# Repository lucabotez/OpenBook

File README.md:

Botez Luca, 334CA

# OpenBook

## About
This project is a minimalist eBook Reader called OpenBook, built on the ESP32-C6 platform and equipped with a 7.5-inch e-paper display, a Li-Po battery, USB-C charging, and physical control buttons.

The device is designed to be energy-efficient and easy to use, featuring a simple interface controlled via GPIOs, with text display functions aimed at providing an optimal e-reading experience.

## Block Diagram

## BOM (Bill of Materials)

| Component | Purchase Link | Datasheet |
|-----------|---------------|-----------|
| BOOT_BUTTON | [https://ro.mouser.com/ProductDetail/Panasonic/EVQ-P7L01P](https://ro.mouser.com/ProductDetail/Panasonic/EVQ-P7L01P?qs=rJ%252BziJWpyszWhhNszc02jQ%3D%3D&_gl=1*xzqk3l*_ga*dW5kZWZpbmVk*_ga_15W4STQT4T*dW5kZWZpbmVk*_ga_1KQLCYKRX3*dW5kZWZpbmVk) | https://componentsearchengine.com/Datasheets/2/EVQP7L01P.pdf |
| C1 | [https://ro.mouser.com/ProductDetail/YAGEO/CC0402MRX5R5BB106](https://ro.mouser.com/ProductDetail/YAGEO/CC0402MRX5R5BB106?qs=zEY9bCHj09eCmUJdZuS5Lg%3D%3D) | https://componentsearchengine.com/Datasheets/2/CC0402MRX5R5BB106.pdf |
| C1_BAT | [https://ro.mouser.com/ProductDetail/YAGEO/CC0402MRX5R5BB106](https://ro.mouser.com/ProductDetail/YAGEO/CC0402MRX5R5BB106?qs=zEY9bCHj09eCmUJdZuS5Lg%3D%3D) | https://componentsearchengine.com/Datasheets/2/CC0402MRX5R5BB106.pdf |
| C1_BAT2 | [https://ro.mouser.com/ProductDetail/YAGEO/CC0402MRX5R5BB106](https://ro.mouser.com/ProductDetail/YAGEO/CC0402MRX5R5BB106?qs=zEY9bCHj09eCmUJdZuS5Lg%3D%3D) | https://componentsearchengine.com/Datasheets/2/CC0402MRX5R5BB106.pdf |
| C2 | [https://ro.mouser.com/ProductDetail/YAGEO/CC0402MRX5R5BB106](https://ro.mouser.com/ProductDetail/YAGEO/CC0402MRX5R5BB106?qs=zEY9bCHj09eCmUJdZuS5Lg%3D%3D) | https://componentsearchengine.com/Datasheets/2/CC0402MRX5R5BB106.pdf |
| C2_BAT | [https://ro.mouser.com/ProductDetail/YAGEO/CC0402MRX5R5BB106](https://ro.mouser.com/ProductDetail/YAGEO/CC0402MRX5R5BB106?qs=zEY9bCHj09eCmUJdZuS5Lg%3D%3D) | https://componentsearchengine.com/Datasheets/2/CC0402MRX5R5BB106.pdf |
| C3 | [https://ro.mouser.com/ProductDetail/YAGEO/CC0402MRX5R5BB106](https://ro.mouser.com/ProductDetail/YAGEO/CC0402MRX5R5BB106?qs=zEY9bCHj09eCmUJdZuS5Lg%3D%3D) | https://componentsearchengine.com/Datasheets/2/CC0402MRX5R5BB106.pdf |
| C4 | [https://ro.mouser.com/ProductDetail/YAGEO/CC0402MRX5R5BB106](https://ro.mouser.com/ProductDetail/YAGEO/CC0402MRX5R5BB106?qs=zEY9bCHj09eCmUJdZuS5Lg%3D%3D) | https://componentsearchengine.com/Datasheets/2/CC0402MRX5R5BB106.pdf |
| C4_USB | [https://ro.mouser.com/ProductDetail/YAGEO/CC0402MRX5R5BB106](https://ro.mouser.com/ProductDetail/YAGEO/CC0402MRX5R5BB106?qs=zEY9bCHj09eCmUJdZuS5Lg%3D%3D) | https://componentsearchengine.com/Datasheets/2/CC0402MRX5R5BB106.pdf |
| C5 | [https://ro.mouser.com/ProductDetail/YAGEO/CC0402MRX5R5BB106](https://ro.mouser.com/ProductDetail/YAGEO/CC0402MRX5R5BB106?qs=zEY9bCHj09eCmUJdZuS5Lg%3D%3D) | https://componentsearchengine.com/Datasheets/2/CC0402MRX5R5BB106.pdf |
| C5_USB | [https://ro.mouser.com/ProductDetail/YAGEO/CC0402MRX5R5BB106](https://ro.mouser.com/ProductDetail/YAGEO/CC0402MRX5R5BB106?qs=zEY9bCHj09eCmUJdZuS5Lg%3D%3D) | https://componentsearchengine.com/Datasheets/2/CC0402MRX5R5BB106.pdf |
| C6 | [https://ro.mouser.com/ProductDetail/YAGEO/CC0402MRX5R5BB106](https://ro.mouser.com/ProductDetail/YAGEO/CC0402MRX5R5BB106?qs=zEY9bCHj09eCmUJdZuS5Lg%3D%3D) | https://componentsearchengine.com/Datasheets/2/CC0402MRX5R5BB106.pdf |
| C7 | [https://ro.mouser.com/ProductDetail/YAGEO/CC0402MRX5R5BB106](https://ro.mouser.com/ProductDetail/YAGEO/CC0402MRX5R5BB106?qs=zEY9bCHj09eCmUJdZuS5Lg%3D%3D) | https://componentsearchengine.com/Datasheets/2/CC0402MRX5R5BB106.pdf |
| C8 | [https://ro.mouser.com/ProductDetail/YAGEO/CC0402MRX5R5BB106](https://ro.mouser.com/ProductDetail/YAGEO/CC0402MRX5R5BB106?qs=zEY9bCHj09eCmUJdZuS5Lg%3D%3D) | https://componentsearchengine.com/Datasheets/2/CC0402MRX5R5BB106.pdf |
| C9 | [https://ro.mouser.com/ProductDetail/YAGEO/CC0402MRX5R5BB106](https://ro.mouser.com/ProductDetail/YAGEO/CC0402MRX5R5BB106?qs=zEY9bCHj09eCmUJdZuS5Lg%3D%3D) | https://componentsearchengine.com/Datasheets/2/CC0402MRX5R5BB106.pdf |
| C10 | [https://ro.mouser.com/ProductDetail/YAGEO/CC0402MRX5R5BB106](https://ro.mouser.com/ProductDetail/YAGEO/CC0402MRX5R5BB106?qs=zEY9bCHj09eCmUJdZuS5Lg%3D%3D) | https://componentsearchengine.com/Datasheets/2/CC0402MRX5R5BB106.pdf |
| C10_SUPERCAP | [https://ro.mouser.com/ProductDetail/Seiko-Semiconductors/CPH3225A](https://ro.mouser.com/ProductDetail/Seiko-Semiconductors/CPH3225A?qs=3etwrb1wR%252BhUOph6lAO7eg%3D%3D) | https://ro.mouser.com/datasheet/2/360/Seiko_Instruments_MicroBattery_E_20230330_2024Jan_-3561061.pdf |
| CHANGE_BUTTON | [https://ro.mouser.com/ProductDetail/Panasonic/EVQ-P7L01P](https://ro.mouser.com/ProductDetail/Panasonic/EVQ-P7L01P?qs=rJ%252BziJWpyszWhhNszc02jQ%3D%3D&_gl=1*xzqk3l*_ga*dW5kZWZpbmVk*_ga_15W4STQT4T*dW5kZWZpbmVk*_ga_1KQLCYKRX3*dW5kZWZpbmVk) | https://componentsearchengine.com/Datasheets/2/EVQP7L01P.pdf |
| C_DELAY | [https://ro.mouser.com/ProductDetail/YAGEO/CC0402MRX5R5BB106](https://ro.mouser.com/ProductDetail/YAGEO/CC0402MRX5R5BB106?qs=zEY9bCHj09eCmUJdZuS5Lg%3D%3D) | https://componentsearchengine.com/Datasheets/2/CC0402MRX5R5BB106.pdf |
| D1 | [https://ro.mouser.com/ProductDetail/STMicroelectronics/USBLC6-2SC6Y](https://ro.mouser.com/ProductDetail/STMicroelectronics/USBLC6-2SC6Y?qs=gNDSiZmRJS%2FOgDexvXkdow%3D%3D) | https://ro.mouser.com/datasheet/2/389/usblc6_2sc6y-1852505.pdf |
| D2 | [https://ro.mouser.com/ProductDetail/KYOCERA-AVX/SD0805S020S1R0](https://ro.mouser.com/ProductDetail/KYOCERA-AVX/SD0805S020S1R0?qs=jCA%252BPfw4LHbpkAoSnwrdjw%3D%3D) | https://ro.mouser.com/datasheet/2/40/schottky-3165252.pdf |
| D3 | [https://ro.mouser.com/ProductDetail/Vishay-Semiconductors/MBR0530](https://ro.mouser.com/ProductDetail/Vishay-Semiconductors/MBR0530?qs=HoksaeI1MJOP4GvpzMgEDg%3D%3D) | https://www.onsemi.com/pdf/datasheet/mbr0530-d.pdf |
| D4 | [https://ro.mouser.com/ProductDetail/Vishay-Semiconductors/MBR0530](https://ro.mouser.com/ProductDetail/Vishay-Semiconductors/MBR0530?qs=HoksaeI1MJOP4GvpzMgEDg%3D%3D) | https://www.onsemi.com/pdf/datasheet/mbr0530-d.pdf |
| D5 | [https://ro.mouser.com/ProductDetail/Vishay-Semiconductors/MBR0530](https://ro.mouser.com/ProductDetail/Vishay-Semiconductors/MBR0530?qs=HoksaeI1MJOP4GvpzMgEDg%3D%3D) | https://www.onsemi.com/pdf/datasheet/mbr0530-d.pdf |
| D6 | [https://ro.mouser.com/ProductDetail/Littelfuse/PGB1010603MR](https://ro.mouser.com/ProductDetail/Littelfuse/PGB1010603MR?qs=gu7KAQ731URLg4GSnNNN7Q%3D%3D) | https://www.littelfuse.com/assetdocs/pulseguard-esd-suppressors-pgb1-datasheet?assetguid=8a337998-d54d-466b-be4e-dc5bcd1f9321 |
| D7 | [https://ro.mouser.com/ProductDetail/KYOCERA-AVX/SD0805S020S1R0](https://ro.mouser.com/ProductDetail/KYOCERA-AVX/SD0805S020S1R0?qs=jCA%252BPfw4LHbpkAoSnwrdjw%3D%3D) | https://ro.mouser.com/datasheet/2/40/schottky-3165252.pdf |
| D8 | [https://ro.mouser.com/ProductDetail/Littelfuse/PGB1010603MR](https://ro.mouser.com/ProductDetail/Littelfuse/PGB1010603MR?qs=gu7KAQ731URLg4GSnNNN7Q%3D%3D) | https://www.littelfuse.com/assetdocs/pulseguard-esd-suppressors-pgb1-datasheet?assetguid=8a337998-d54d-466b-be4e-dc5bcd1f9321 |
| D9 | [https://ro.mouser.com/ProductDetail/Littelfuse/PGB1010603MR](https://ro.mouser.com/ProductDetail/Littelfuse/PGB1010603MR?qs=gu7KAQ731URLg4GSnNNN7Q%3D%3D) | https://www.littelfuse.com/assetdocs/pulseguard-esd-suppressors-pgb1-datasheet?assetguid=8a337998-d54d-466b-be4e-dc5bcd1f9321 |
| D10 | [https://ro.mouser.com/ProductDetail/Littelfuse/PGB1010603MR](https://ro.mouser.com/ProductDetail/Littelfuse/PGB1010603MR?qs=gu7KAQ731URLg4GSnNNN7Q%3D%3D) | https://www.littelfuse.com/assetdocs/pulseguard-esd-suppressors-pgb1-datasheet?assetguid=8a337998-d54d-466b-be4e-dc5bcd1f9321 |
| D11 | [https://ro.mouser.com/ProductDetail/Littelfuse/PGB1010603MR](https://ro.mouser.com/ProductDetail/Littelfuse/PGB1010603MR?qs=gu7KAQ731URLg4GSnNNN7Q%3D%3D) | https://www.littelfuse.com/assetdocs/pulseguard-esd-suppressors-pgb1-datasheet?assetguid=8a337998-d54d-466b-be4e-dc5bcd1f9321 |
| D12 | [https://ro.mouser.com/ProductDetail/Littelfuse/PGB1010603MR](https://ro.mouser.com/ProductDetail/Littelfuse/PGB1010603MR?qs=gu7KAQ731URLg4GSnNNN7Q%3D%3D) | https://www.littelfuse.com/assetdocs/pulseguard-esd-suppressors-pgb1-datasheet?assetguid=8a337998-d54d-466b-be4e-dc5bcd1f9321 |
| EPD_C1 | [https://ro.mouser.com/ProductDetail/YAGEO/CC0402MRX5R5BB106](https://ro.mouser.com/ProductDetail/YAGEO/CC0402MRX5R5BB106?qs=zEY9bCHj09eCmUJdZuS5Lg%3D%3D) | https://componentsearchengine.com/Datasheets/2/CC0402MRX5R5BB106.pdf |
| EPD_C2 | [https://ro.mouser.com/ProductDetail/YAGEO/CC0402MRX5R5BB106](https://ro.mouser.com/ProductDetail/YAGEO/CC0402MRX5R5BB106?qs=zEY9bCHj09eCmUJdZuS5Lg%3D%3D) | https://componentsearchengine.com/Datasheets/2/CC0402MRX5R5BB106.pdf |
| EPD_C3 | [https://ro.mouser.com/ProductDetail/YAGEO/CC0402MRX5R5BB106](https://ro.mouser.com/ProductDetail/YAGEO/CC0402MRX5R5BB106?qs=zEY9bCHj09eCmUJdZuS5Lg%3D%3D) | https://componentsearchengine.com/Datasheets/2/CC0402MRX5R5BB106.pdf |
| EPD_C4 | [https://ro.mouser.com/ProductDetail/YAGEO/CC0402MRX5R5BB106](https://ro.mouser.com/ProductDetail/YAGEO/CC0402MRX5R5BB106?qs=zEY9bCHj09eCmUJdZuS5Lg%3D%3D) | https://componentsearchengine.com/Datasheets/2/CC0402MRX5R5BB106.pdf |
| EPD_C5 | [https://ro.mouser.com/ProductDetail/YAGEO/CC0402MRX5R5BB106](https://ro.mouser.com/ProductDetail/YAGEO/CC0402MRX5R5BB106?qs=zEY9bCHj09eCmUJdZuS5Lg%3D%3D) | https://componentsearchengine.com/Datasheets/2/CC0402MRX5R5BB106.pdf |
| EPD_C6 | [https://ro.mouser.com/ProductDetail/YAGEO/CC0402MRX5R5BB106](https://ro.mouser.com/ProductDetail/YAGEO/CC0402MRX5R5BB106?qs=zEY9bCHj09eCmUJdZuS5Lg%3D%3D) | https://componentsearchengine.com/Datasheets/2/CC0402MRX5R5BB106.pdf |
| EPD_C7 | [https://ro.mouser.com/ProductDetail/YAGEO/CC0402MRX5R5BB106](https://ro.mouser.com/ProductDetail/YAGEO/CC0402MRX5R5BB106?qs=zEY9bCHj09eCmUJdZuS5Lg%3D%3D) | https://componentsearchengine.com/Datasheets/2/CC0402MRX5R5BB106.pdf |
| EPD_C8 | [https://ro.mouser.com/ProductDetail/YAGEO/CC0402MRX5R5BB106](https://ro.mouser.com/ProductDetail/YAGEO/CC0402MRX5R5BB106?qs=zEY9bCHj09eCmUJdZuS5Lg%3D%3D) | https://componentsearchengine.com/Datasheets/2/CC0402MRX5R5BB106.pdf |
| EPD_C9 | [https://ro.mouser.com/ProductDetail/YAGEO/CC0402MRX5R5BB106](https://ro.mouser.com/ProductDetail/YAGEO/CC0402MRX5R5BB106?qs=zEY9bCHj09eCmUJdZuS5Lg%3D%3D) | https://componentsearchengine.com/Datasheets/2/CC0402MRX5R5BB106.pdf |
| EPD_C10 | [https://ro.mouser.com/ProductDetail/YAGEO/CC0402MRX5R5BB106](https://ro.mouser.com/ProductDetail/YAGEO/CC0402MRX5R5BB106?qs=zEY9bCHj09eCmUJdZuS5Lg%3D%3D) | https://componentsearchengine.com/Datasheets/2/CC0402MRX5R5BB106.pdf |
| EPD_C11 | [https://ro.mouser.com/ProductDetail/YAGEO/CC0402MRX5R5BB106](https://ro.mouser.com/ProductDetail/YAGEO/CC0402MRX5R5BB106?qs=zEY9bCHj09eCmUJdZuS5Lg%3D%3D) | https://componentsearchengine.com/Datasheets/2/CC0402MRX5R5BB106.pdf |
| EPD_C12 | [https://ro.mouser.com/ProductDetail/YAGEO/CC0402MRX5R5BB106](https://ro.mouser.com/ProductDetail/YAGEO/CC0402MRX5R5BB106?qs=zEY9bCHj09eCmUJdZuS5Lg%3D%3D) | https://componentsearchengine.com/Datasheets/2/CC0402MRX5R5BB106.pdf |
| IC1 | [https://ro.mouser.com/ProductDetail/ROHM-Semiconductor/BD5229G-TR](https://ro.mouser.com/ProductDetail/ROHM-Semiconductor/BD5229G-TR?qs=4kLU8WoGk0vvnhrrYwdszw%3D%3D) | https://fscdn.rohm.com/en/products/databook/datasheet/ic/power/voltage_detector/bd52xxg-e.pdf |
| IC4 | [https://ro.mouser.com/ProductDetail/Torex-Semiconductor/XC6220A331MR-G](https://ro.mouser.com/ProductDetail/Torex-Semiconductor/XC6220A331MR-G?qs=AsjdqWjXhJ8ZSWznL1J0gg%3D%3D) | https://ro.mouser.com/datasheet/2/760/xc6220-3371556.pdf |
| J1 | [https://ro.mouser.com/ProductDetail/Hirose-Connector/FH34SRJ-24S-0.5SH99](https://ro.mouser.com/ProductDetail/Hirose-Connector/FH34SRJ-24S-0.5SH99?qs=vcbW%252B4%252BSTIpKBl5ap9J8Fw%3D%3D) | https://ro.mouser.com/datasheet/2/185/FH34SRJ_24S_0_5SH_99__CL0580_1255_6_99_2DDrawing_0-1615044.pdf |
| J2 | [https://ro.mouser.com/ProductDetail/GCT/USB4110-GF-A](https://ro.mouser.com/ProductDetail/GCT/USB4110-GF-A?qs=KUoIvG%2F9IlYiZvIXQjyJeA%3D%3D) | https://ro.mouser.com/datasheet/2/837/GCT_USB4110_Product_Drawing___20k_cycles-3455479.pdf |
| J3 | [https://ro.mouser.com/ProductDetail/SparkFun/PRT-14417](https://ro.mouser.com/ProductDetail/SparkFun/PRT-14417?qs=wd5RIQLrsJhgdz%2FpmZ%2F3GQ%3D%3D) | https://ro.mouser.com/datasheet/2/813/Qwiic_Connector_Datasheet-1223982.pdf |
| J4 | https://store.comet.srl.ro/Catalogue/Product/43497/ | https://store.comet.bg/download-file.php?id=8824 |
| L1 | [https://ro.mouser.com/ProductDetail/Wurth-Elektronik/744043680](https://ro.mouser.com/ProductDetail/Wurth-Elektronik/744043680?qs=PGXP4M47uW6VkZq%252BkzjrHA%3D%3D) | https://www.we-online.com/components/products/datasheet/744043680.pdf |
| PFMF.050.1 | [https://ro.mouser.com/ProductDetail/KEMET/VE1812K401R050](https://ro.mouser.com/ProductDetail/KEMET/VE1812K401R050?qs=OycAS1CGnlizCtaoDVbQTA%3D%3D) | https://ro.mouser.com/datasheet/2/447/KEM_V0003_VE-3316901.pdf |
| Q1 | [https://ro.mouser.com/ProductDetail/Diodes-Incorporated/DMG2305UX-7](https://ro.mouser.com/ProductDetail/Diodes-Incorporated/DMG2305UX-7?qs=L1DZKBg7t5F%2FNBHrjfxC%252Bg%3D%3D) | https://www.diodes.com/assets/Datasheets/DMG2305UX.pdf |
| Q2 | [https://ro.mouser.com/ProductDetail/Diodes-Incorporated/DMG2305UX-7](https://ro.mouser.com/ProductDetail/Diodes-Incorporated/DMG2305UX-7?qs=L1DZKBg7t5F%2FNBHrjfxC%252Bg%3D%3D) | https://www.diodes.com/assets/Datasheets/DMG2305UX.pdf |
| Q3 | [https://ro.mouser.com/ProductDetail/Vishay-Semiconductors/SI1308EDL-T1-GE3](https://ro.mouser.com/ProductDetail/Vishay-Semiconductors/SI1308EDL-T1-GE3?qs=bX1%252BNvsK%2FBramh9tgpOaEw%3D%3D) | https://www.vishay.com/docs/63399/si1308edl.pdf |
| R1 | [https://ro.mouser.com/ProductDetail/YAGEO/RC0402FR-07100KL](https://ro.mouser.com/ProductDetail/YAGEO/RC0402FR-07100KL?qs=mnq%2FyloZIXzTlUn7JAHSWg%3D%3D) | https://ro.mouser.com/datasheet/2/447/YAGEO_PYu_RC_Group_51_RoHS_L_12-3313492.pdf |
| R1_PINH | [https://ro.mouser.com/ProductDetail/YAGEO/RC0402FR-07100KL](https://ro.mouser.com/ProductDetail/YAGEO/RC0402FR-07100KL?qs=mnq%2FyloZIXzTlUn7JAHSWg%3D%3D) | https://ro.mouser.com/datasheet/2/447/YAGEO_PYu_RC_Group_51_RoHS_L_12-3313492.pdf |
| R1_PINH1 | [https://ro.mouser.com/ProductDetail/YAGEO/RC0402FR-07100KL](https://ro.mouser.com/ProductDetail/YAGEO/RC0402FR-07100KL?qs=mnq%2FyloZIXzTlUn7JAHSWg%3D%3D) | https://ro.mouser.com/datasheet/2/447/YAGEO_PYu_RC_Group_51_RoHS_L_12-3313492.pdf |
| R1_BAT | [https://ro.mouser.com/ProductDetail/YAGEO/RC0402FR-07100KL](https://ro.mouser.com/ProductDetail/YAGEO/RC0402FR-07100KL?qs=mnq%2FyloZIXzTlUn7JAHSWg%3D%3D) | https://ro.mouser.com/datasheet/2/447/YAGEO_PYu_RC_Group_51_RoHS_L_12-3313492.pdf |
| R1_PWRUSB | [https://ro.mouser.com/ProductDetail/YAGEO/RC0402FR-07100KL](https://ro.mouser.com/ProductDetail/YAGEO/RC0402FR-07100KL?qs=mnq%2FyloZIXzTlUn7JAHSWg%3D%3D) | https://ro.mouser.com/datasheet/2/447/YAGEO_PYu_RC_Group_51_RoHS_L_12-3313492.pdf |
| R2 | [https://ro.mouser.com/ProductDetail/YAGEO/RC0402FR-07100KL](https://ro.mouser.com/ProductDetail/YAGEO/RC0402FR-07100KL?qs=mnq%2FyloZIXzTlUn7JAHSWg%3D%3D) | https://ro.mouser.com/datasheet/2/447/YAGEO_PYu_RC_Group_51_RoHS_L_12-3313492.pdf |
| R2_PINH | [https://ro.mouser.com/ProductDetail/YAGEO/RC0402FR-07100KL](https://ro.mouser.com/ProductDetail/YAGEO/RC0402FR-07100KL?qs=mnq%2FyloZIXzTlUn7JAHSWg%3D%3D) | https://ro.mouser.com/datasheet/2/447/YAGEO_PYu_RC_Group_51_RoHS_L_12-3313492.pdf |
| R2_PINH1 | [https://ro.mouser.com/ProductDetail/YAGEO/RC0402FR-07100KL](https://ro.mouser.com/ProductDetail/YAGEO/RC0402FR-07100KL?qs=mnq%2FyloZIXzTlUn7JAHSWg%3D%3D) | https://ro.mouser.com/datasheet/2/447/YAGEO_PYu_RC_Group_51_RoHS_L_12-3313492.pdf |
| R2_USB | [https://ro.mouser.com/ProductDetail/YAGEO/RC0402FR-07100KL](https://ro.mouser.com/ProductDetail/YAGEO/RC0402FR-07100KL?qs=mnq%2FyloZIXzTlUn7JAHSWg%3D%3D) | https://ro.mouser.com/datasheet/2/447/YAGEO_PYu_RC_Group_51_RoHS_L_12-3313492.pdf |
| R2_USB1 | [https://ro.mouser.com/ProductDetail/YAGEO/RC0402FR-07100KL](https://ro.mouser.com/ProductDetail/YAGEO/RC0402FR-07100KL?qs=mnq%2FyloZIXzTlUn7JAHSWg%3D%3D) | https://ro.mouser.com/datasheet/2/447/YAGEO_PYu_RC_Group_51_RoHS_L_12-3313492.pdf |
| R2_BAT | [https://ro.mouser.com/ProductDetail/YAGEO/RC0402FR-07100KL](https://ro.mouser.com/ProductDetail/YAGEO/RC0402FR-07100KL?qs=mnq%2FyloZIXzTlUn7JAHSWg%3D%3D) | https://ro.mouser.com/datasheet/2/447/YAGEO_PYu_RC_Group_51_RoHS_L_12-3313492.pdf |
| R3 | [https://ro.mouser.com/ProductDetail/YAGEO/RC0402FR-07100KL](https://ro.mouser.com/ProductDetail/YAGEO/RC0402FR-07100KL?qs=mnq%2FyloZIXzTlUn7JAHSWg%3D%3D) | https://ro.mouser.com/datasheet/2/447/YAGEO_PYu_RC_Group_51_RoHS_L_12-3313492.pdf |
| R4 | [https://ro.mouser.com/ProductDetail/YAGEO/RC0402FR-07100KL](https://ro.mouser.com/ProductDetail/YAGEO/RC0402FR-07100KL?qs=mnq%2FyloZIXzTlUn7JAHSWg%3D%3D) | https://ro.mouser.com/datasheet/2/447/YAGEO_PYu_RC_Group_51_RoHS_L_12-3313492.pdf |
| R5 | [https://ro.mouser.com/ProductDetail/YAGEO/RC0402FR-07100KL](https://ro.mouser.com/ProductDetail/YAGEO/RC0402FR-07100KL?qs=mnq%2FyloZIXzTlUn7JAHSWg%3D%3D) | https://ro.mouser.com/datasheet/2/447/YAGEO_PYu_RC_Group_51_RoHS_L_12-3313492.pdf |
| R6 | [https://ro.mouser.com/ProductDetail/YAGEO/RC0402FR-07100KL](https://ro.mouser.com/ProductDetail/YAGEO/RC0402FR-07100KL?qs=mnq%2FyloZIXzTlUn7JAHSWg%3D%3D) | https://ro.mouser.com/datasheet/2/447/YAGEO_PYu_RC_Group_51_RoHS_L_12-3313492.pdf |
| R7 | [https://ro.mouser.com/ProductDetail/YAGEO/RC0402FR-07100KL](https://ro.mouser.com/ProductDetail/YAGEO/RC0402FR-07100KL?qs=mnq%2FyloZIXzTlUn7JAHSWg%3D%3D) | https://ro.mouser.com/datasheet/2/447/YAGEO_PYu_RC_Group_51_RoHS_L_12-3313492.pdf |
| R8 | [https://ro.mouser.com/ProductDetail/YAGEO/RC0402FR-07100KL](https://ro.mouser.com/ProductDetail/YAGEO/RC0402FR-07100KL?qs=mnq%2FyloZIXzTlUn7JAHSWg%3D%3D) | https://ro.mouser.com/datasheet/2/447/YAGEO_PYu_RC_Group_51_RoHS_L_12-3313492.pdf |
| R9 | [https://ro.mouser.com/ProductDetail/YAGEO/RC0402FR-07100KL](https://ro.mouser.com/ProductDetail/YAGEO/RC0402FR-07100KL?qs=mnq%2FyloZIXzTlUn7JAHSWg%3D%3D) | https://ro.mouser.com/datasheet/2/447/YAGEO_PYu_RC_Group_51_RoHS_L_12-3313492.pdf |
| R10 | [https://ro.mouser.com/ProductDetail/YAGEO/RC0402FR-07100KL](https://ro.mouser.com/ProductDetail/YAGEO/RC0402FR-07100KL?qs=mnq%2FyloZIXzTlUn7JAHSWg%3D%3D) | https://ro.mouser.com/datasheet/2/447/YAGEO_PYu_RC_Group_51_RoHS_L_12-3313492.pdf |
| RESET_BUTTON | [https://ro.mouser.com/ProductDetail/Panasonic/EVQ-P7L01P](https://ro.mouser.com/ProductDetail/Panasonic/EVQ-P7L01P?qs=rJ%252BziJWpyszWhhNszc02jQ%3D%3D&_gl=1*xzqk3l*_ga*dW5kZWZpbmVk*_ga_15W4STQT4T*dW5kZWZpbmVk*_ga_1KQLCYKRX3*dW5kZWZpbmVk) | https://componentsearchengine.com/Datasheets/2/EVQP7L01P.pdf |
| R_BOOT | [https://ro.mouser.com/ProductDetail/YAGEO/RC0402FR-07100KL](https://ro.mouser.com/ProductDetail/YAGEO/RC0402FR-07100KL?qs=mnq%2FyloZIXzTlUn7JAHSWg%3D%3D) | https://ro.mouser.com/datasheet/2/447/YAGEO_PYu_RC_Group_51_RoHS_L_12-3313492.pdf |
| R_CAPACITOR | [https://ro.mouser.com/ProductDetail/YAGEO/RC0402FR-07100KL](https://ro.mouser.com/ProductDetail/YAGEO/RC0402FR-07100KL?qs=mnq%2FyloZIXzTlUn7JAHSWg%3D%3D) | https://ro.mouser.com/datasheet/2/447/YAGEO_PYu_RC_Group_51_RoHS_L_12-3313492.pdf |
| R_CHANGE | [https://ro.mouser.com/ProductDetail/YAGEO/RC0402FR-07100KL](https://ro.mouser.com/ProductDetail/YAGEO/RC0402FR-07100KL?qs=mnq%2FyloZIXzTlUn7JAHSWg%3D%3D) | https://ro.mouser.com/datasheet/2/447/YAGEO_PYu_RC_Group_51_RoHS_L_12-3313492.pdf |
| R_CL1 | [https://ro.mouser.com/ProductDetail/YAGEO/RC0402FR-07100KL](https://ro.mouser.com/ProductDetail/YAGEO/RC0402FR-07100KL?qs=mnq%2FyloZIXzTlUn7JAHSWg%3D%3D) | https://ro.mouser.com/datasheet/2/447/YAGEO_PYu_RC_Group_51_RoHS_L_12-3313492.pdf |
| R_RESET | [https://ro.mouser.com/ProductDetail/YAGEO/RC0402FR-07100KL](https://ro.mouser.com/ProductDetail/YAGEO/RC0402FR-07100KL?qs=mnq%2FyloZIXzTlUn7JAHSWg%3D%3D) | https://ro.mouser.com/datasheet/2/447/YAGEO_PYu_RC_Group_51_RoHS_L_12-3313492.pdf |
| SENSOR2 | [https://ro.mouser.com/ProductDetail/Bosch-Sensortec/BME680](https://ro.mouser.com/ProductDetail/Bosch-Sensortec/BME680?qs=v271MhAjFHjo0yA%2FC4OnDQ%3D%3D) | https://ro.mouser.com/datasheet/2/783/BST_BME680_DS001-1509608.pdf |
| SJ1 | https://grabcad.com/library/solder-jumpers-1 | https://grabcad.com/library/solder-jumpers-1 |
| TP1 | CUSTOM | CUSTOM |
| TP2 | CUSTOM | CUSTOM |
| TP3 | CUSTOM | CUSTOM |
| TP4 | CUSTOM | CUSTOM |
| TP5 | CUSTOM | CUSTOM |
| TP6 | CUSTOM | CUSTOM |
| TP7 | CUSTOM | CUSTOM |
| TP8 | CUSTOM | CUSTOM |
| TP9 | CUSTOM | CUSTOM |
| TP10 | CUSTOM | CUSTOM |
| TP11 | CUSTOM | CUSTOM |
| TP12 | CUSTOM | CUSTOM |
| TP13 | CUSTOM | CUSTOM |
| TP14 | CUSTOM | CUSTOM |
| TP15 | CUSTOM | CUSTOM |
| TP16 | CUSTOM | CUSTOM |
| TP17 | CUSTOM | CUSTOM |
| U1 | [https://ro.mouser.com/ProductDetail/Winbond/W25Q512JVEIQ](https://ro.mouser.com/ProductDetail/Winbond/W25Q512JVEIQ?qs=l7cgNqFNU1jw6svr3at6tA%3D%3D) | https://ro.mouser.com/datasheet/2/949/Winbond_W25Q512JV_Datasheet-3240039.pdf |
| U2 | [https://ro.mouser.com/ProductDetail/Espressif-Systems/ESP32-C6-WROOM-1-N8](https://ro.mouser.com/ProductDetail/Espressif-Systems/ESP32-C6-WROOM-1-N8?qs=8Wlm6%252BaMh8ST02Gmwp74cw%3D%3D) | https://ro.mouser.com/datasheet/2/891/Espressif_ESP32_C6_WROOM_1__Datasheet_V0_1_PRELIMI-3239987.pdf |
| U3 | [https://ro.mouser.com/ProductDetail/Analog-Devices-Maxim-Integrated/DS3231SN](https://ro.mouser.com/ProductDetail/Analog-Devices-Maxim-Integrated/DS3231SN?qs=1eQvB6Dk1vhUlr8%2FOrV0Fw%3D%3D) | https://ro.mouser.com/datasheet/2/609/DS3231-3421123.pdf |
| U4 | [https://ro.mouser.com/ProductDetail/Analog-Devices-Maxim-Integrated/MAX17048G+T10](https://ro.mouser.com/ProductDetail/Analog-Devices-Maxim-Integrated/MAX17048G%2bT10?qs=D7PJwyCwLAoGnnn8jEPRBQ%3D%3D) | https://ro.mouser.com/datasheet/2/609/MAX17048_MAX17049-3469099.pdf |
| U5 | [https://ro.mouser.com/ProductDetail/Microchip-Technology/MCP73831T-2ACI-OT](https://ro.mouser.com/ProductDetail/Microchip-Technology/MCP73831T-2ACI-OT?qs=yUQqVecv4qvbBQBGbHx0Mw%3D%3D) | https://ro.mouser.com/datasheet/2/268/MCP73831_Family_Data_Sheet_DS20001984H-3441711.pdf |

## Hardware Description

- **ESP32-C6-WROOM-1-N8** – Main microcontroller with integrated **Wi-Fi** and **BLE**; manages communication, sensors, and display.
- **BME688** – Environmental and air quality sensor (**temperature**, **humidity**, **pressure**, **gas**); connected via **I²C**.
- **DS3231SN** – High-precision **RTC (Real-Time Clock)** module for maintaining accurate time; connected via **I²C**.
- **MAX17048** – Battery level monitor with **I²C** interface, provides **State of Charge (SOC)** estimation.
- **SD Card Module** – Used for local data storage; communicates with the ESP32 via **SPI**.
- **E-Ink Display** – Low-power **e-paper display** with **SPI** interface; includes signals like `EPD_CS`, `EPD_DC`, `EPD_RST`, `EPD_BUSY`.
- **W25Q512JVEIQ (64MB NOR Flash)** – External **SPI** flash memory for storing firmware or large datasets.
- **BOOT and RESET Buttons** – Connected to **GPIO** for bootloader activation and system reset control.
- **MCP73831** – **Li-Po battery charging controller**, directly manages the charging process.
- **XC6220A331MR-G (LDO Regulator)** – **3.3V voltage regulator** that powers logic circuits from battery or USB input.
- **USB-C Port (USB4110-GF-A)** – Provides **power input** and **serial interface** for code upload and debugging.

## Detailed ESP32-C6 View

**IO0 - INT_RTC**
- Interrupt signal that can wake up the ESP32 from deep sleep.
- Used by RTC.

**IO1 – 32KHZ**
- The DS3231’s 32.768 kHz clock output, routed to the ESP32‐C6.
- Used by ESP32‐C6.

**IO2 – MISO**
- Hardware-dedicated SPI pin, offering high speed and native compatibility.
- Used by NOR Flash, E-Paper, microSD.

**IO3 - EPD_BUSY**
- GPIO status signal sent by the EPD driver, ESP32 reads it to check if the screen is busy.
- Used by E-Paper Display.

**IO4 – SS_SD**
- Selects the SD card during reading; chosen to avoid conflicts with other CS lines already in use.
- Used by microSD Card.

**IO5 – EPD_DC**
- Control signal specific to EPD to differentiate between commands and data.
- Used by E-Paper Display.

**IO6 – SCK**
- Recommended pin for SPI clock in multi-device implementations; allows SPI bus sharing.
- Used by NOR Flash, E-Paper, microSD.

**IO7 – MOSI**
- Utilized for SPI data transmission, compatible with all connected SPI peripherals.
- Used by NOR Flash, E-Paper, microSD.

**IO9 – IO/BOOT**
- Standard pin for entering programming mode on the ESP32-C6.
- Used by BOOT Button.

**IO10 - EPD_CS**
- Selects the display during SPI transfers; doesn’t interfere with the rest of the SPI devices.
- Used by E-Paper Display.

**IO11 – FLASH_CS**
- Dedicated pin to activate the external Flash memory without interfering with other SPI peripherals.
- Used by External NOR Flash Memory.

**IO12 – USB_D-**
- Direct USB data lines for the built‐in USB peripheral, going to the USB connector.
- Used by USB-C connector.

**IO13 – USB_D+**
- Direct USB data lines for the built‐in USB peripheral, going to the USB connector.
- Used by USB-C connector.

**IO15 – IO/CHANGE**
- General-purpose GPIO chosen for user-defined actions (e.g. Next Page).
- Used by CHANGE Button.

**IO16 – TX**
- Traditional serial line used for flashing the older ESP chips and debug logs.
- Used by Serial Debug.

**IO17 – RX**
- Traditional serial line used for flashing the older ESP chips and debug logs.
- Used by Serial Debug.

**IO18 – RTC_RST**
- External manual reset for the RTC, useful for initial synchronization or watchdog purposes.
- Used by RTC.

**IO19 – I2C_PW**
- 3.3V rail dedicated to powering I2C peripherals (sensors, RTC, battery gauge).
- Used by RTC, BME680, Qwiic.

**IO20 – EPD_3V3_C**
- 3.3V supply line that powers the E‐paper Display module.
- Used by E-Paper Display.

**IO21 – SDA**
- Data line for I2C communication; can be shared between multiple sensors.
- Used by RTC, BME680, Qwiic.

**IO22 – SCL**
- I2C clock line; synchronizes with SDA for reliable transmission.
- Used by RTC, BME680, Qwiic.

**IO23 – EPD_RST**
- Resets the EPD circuit before initialization or display updates.
- Used by E-Paper Display.

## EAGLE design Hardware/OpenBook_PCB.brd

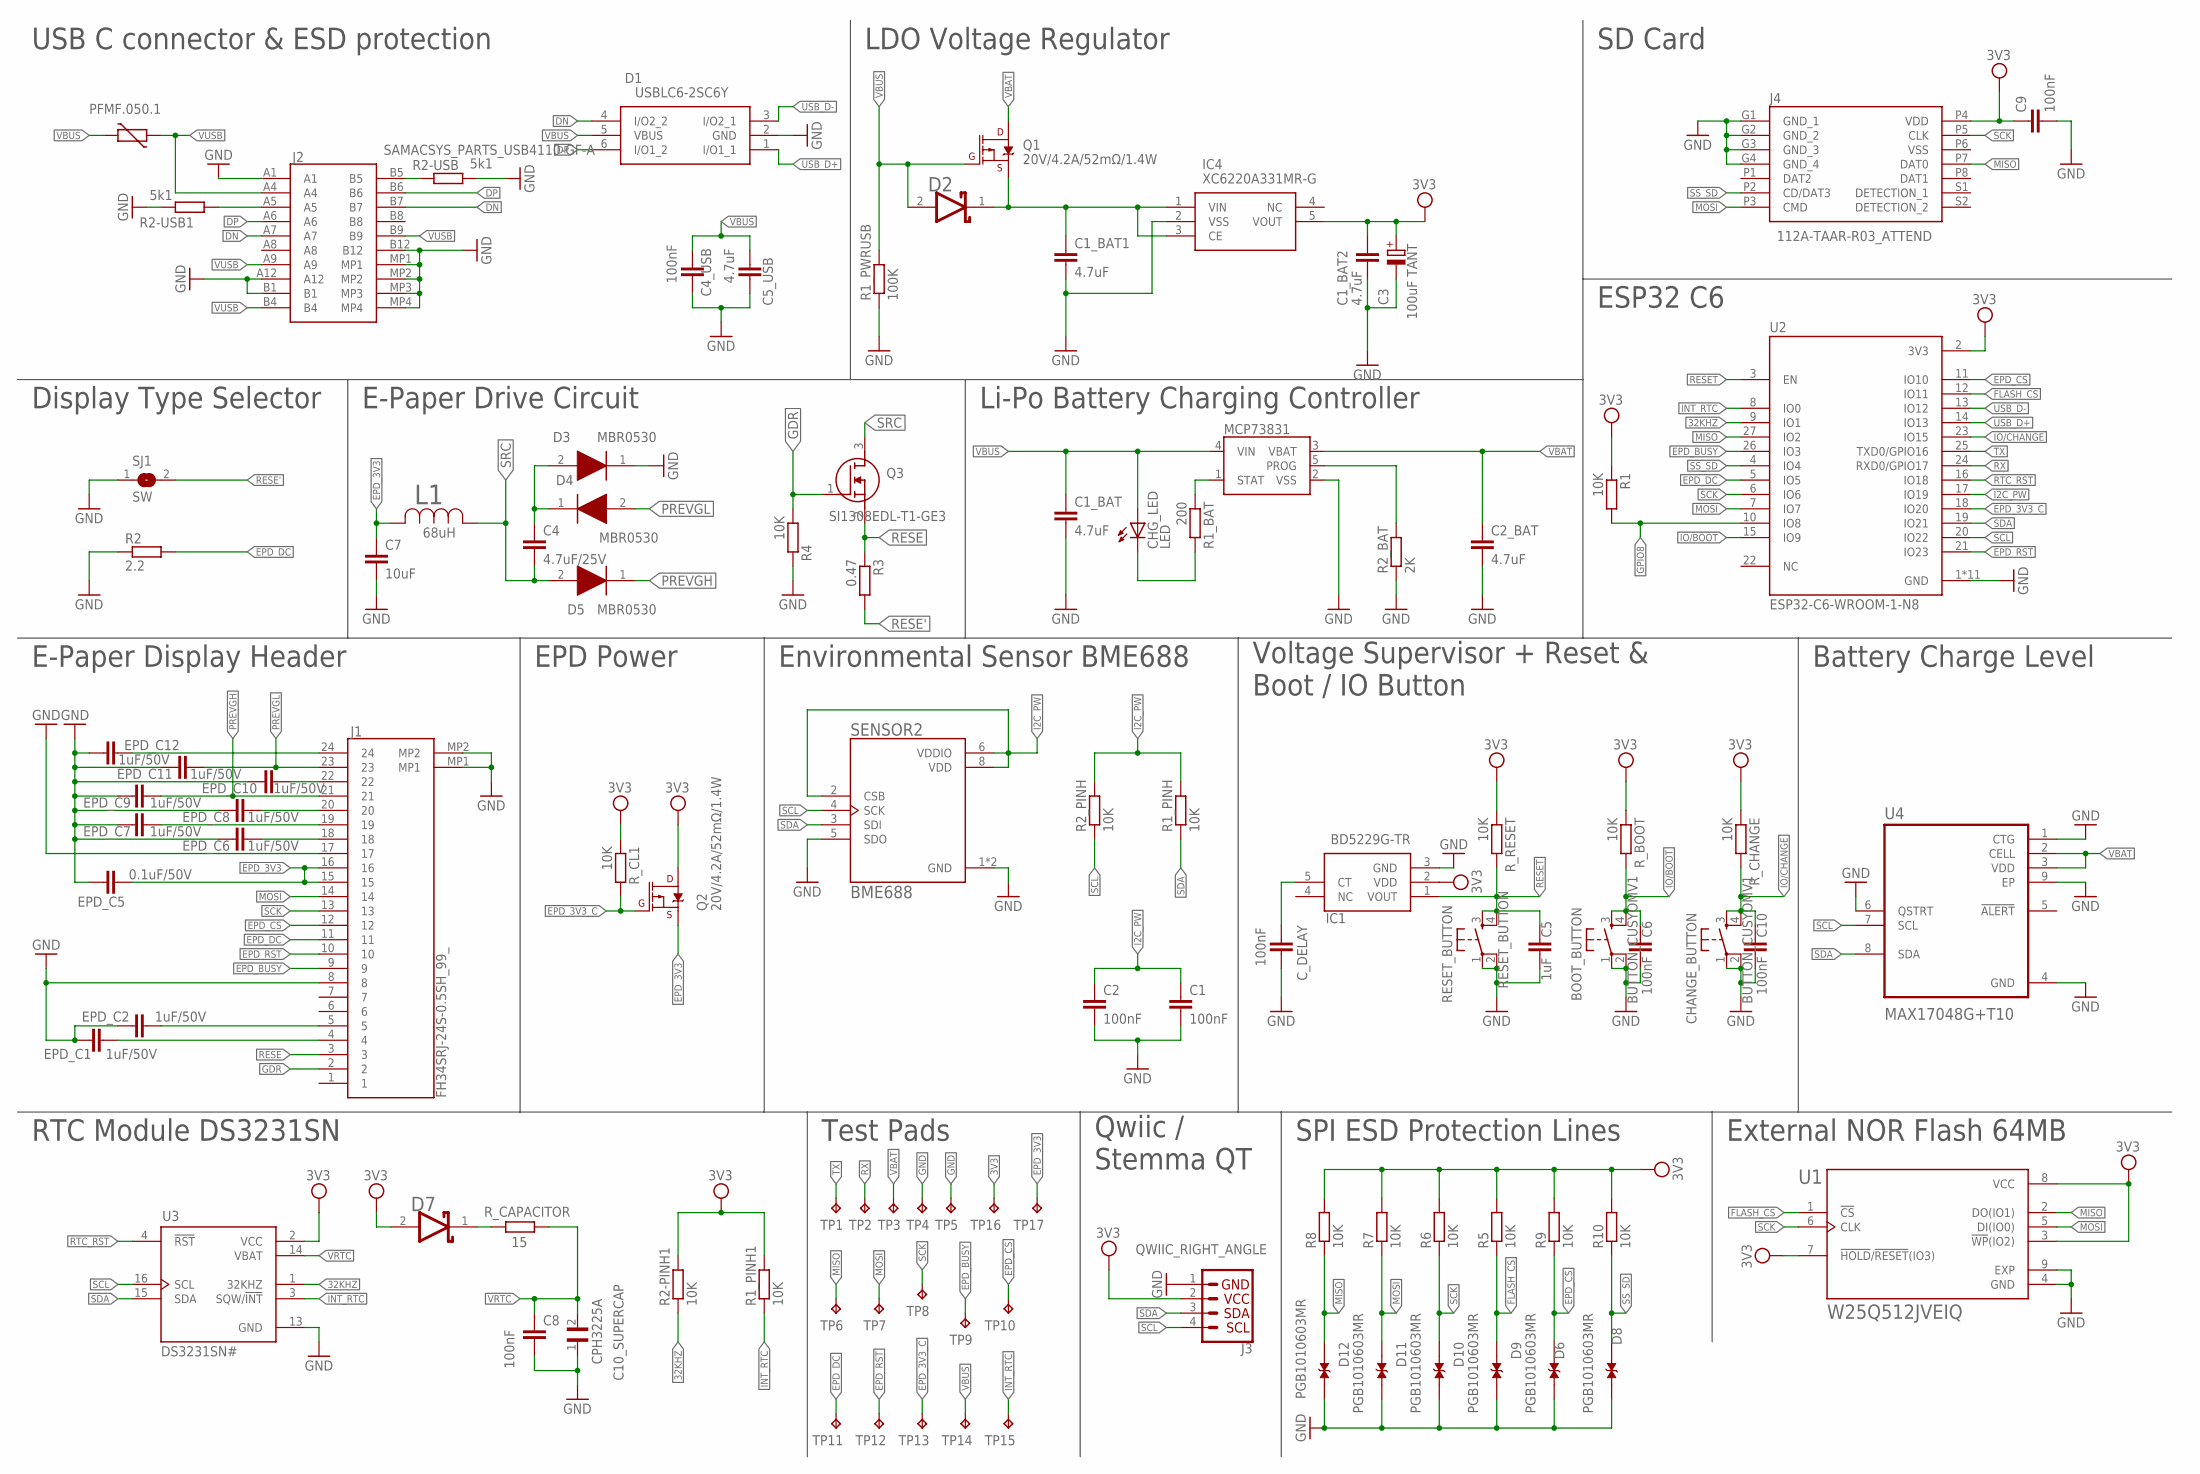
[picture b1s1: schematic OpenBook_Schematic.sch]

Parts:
BOOT_BUTTON: BUTTON_CUSYOMV1; MYBUTTON
C1, C2, C4_USB, C6, C8, C9, C10: 100nF; EAGLE-LTSPICE_C0402
C1_BAT, C1_BAT1, C1_BAT2, C2_BAT, C5_USB: 4.7uF; EAGLE-LTSPICE_C0402
C3: 100uF TANT; RCL_CT3528
C4: 4.7uF/25V; EAGLE-LTSPICE_C0402
C5: 1uF; EAGLE-LTSPICE_C0402
C7: 10uF; EAGLE-LTSPICE_C0402
C10_SUPERCAP: CPH3225A; CAPCP3225X100N
CHANGE_BUTTON: BUTTON_CUSYOMV1; MYBUTTON
CHG_LED: LED; ADAFRUIT_CHIP-LED0603
C_DELAY: 100nF; EAGLE-LTSPICE_C0402
D1: USBLC6-2SC6Y; SOT95P280X145-6N
D2, D7: ESP32_WROVER_AVX---SD0805S020S1R0_AVX_SD0805S020S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; ESP32_WROVER_AVX---SD0805S020S1R0_AVX_SD0805S020S1R0_0
D3, D4, D5: MBR0530; SOD3716X135N
D6, D8, D9, D10, D11, D12: PGB1010603MR; DIOC1608X36N
EPD_C1, EPD_C2, EPD_C6, EPD_C7, EPD_C8, EPD_C9, EPD_C10, EPD_C11, EPD_C12: 1uF/50V; EAGLE-LTSPICE_C0402
EPD_C5: 0.1uF/50V; EAGLE-LTSPICE_C0402
IC1: BD5229G-TR; SOT95P280X125-5N
IC4: XC6220A331MR-G; SOT95P280X120-5N
J1: FH34SRJ-24S-0.5SH_99_; FH34SRJ24S05SH99
J2: SAMACSYS_PARTS_USB4110-GF-A; SAMACSYS_PARTS_USB4110GFA
J3: QWIIC_RIGHT_ANGLE; JST04_1MM_RA
J4: 112A-TAAR-R03_ATTEND; 112ATAARR03ATTEND
L1: 68uH; IND_4828-WE-TPC_WRE
MCP73831: ESP32_WROVER_SPARKFUN-IC-POWER_MCP73831; ESP32_WROVER_SPARKFUN-IC-POWER_SOT23-5
PFMF.050.1: ESP32C6_VARISTORCN1812; ESP32C6_VARISTOR_CT/CN1812
Q1, Q2: 20V/4.2A/52mΩ/1.4W; ESP32_WROVER_SPARKFUN-DISCRETESEMI_SOT23-3
Q3: SI1308EDL-T1-GE3; SOT65P210X110-3N
R1, R1_PINH, R1_PINH1, R2-PINH1, R2_PINH, R4, R5, R6, R7, R8, R9, R10: 10K; ESP32_WROVER_EAGLE-LTSPICE_R0402
R1_BAT: 200; ESP32_WROVER_EAGLE-LTSPICE_R0402
R1_PWRUSB: 100K; ESP32_WROVER_EAGLE-LTSPICE_R0402
R2: 2.2; ESP32_WROVER_EAGLE-LTSPICE_R0402
R2-USB, R2-USB1: 5k1; ESP32_WROVER_EAGLE-LTSPICE_R0402
R2_BAT: 2K; ESP32_WROVER_EAGLE-LTSPICE_R0402
R3: 0.47; ESP32_WROVER_EAGLE-LTSPICE_R0402
RESET_BUTTON: RESET_BUTTON; MYBUTTON
R_BOOT: 10K; ESP32_WROVER_EAGLE-LTSPICE_R0402
R_CAPACITOR: 15; ESP32_WROVER_EAGLE-LTSPICE_R0402
R_CHANGE: 10K; ESP32_WROVER_EAGLE-LTSPICE_R0402
R_CL1: 10K; ESP32_WROVER_EAGLE-LTSPICE_R0402
R_RESET: 10K; ESP32_WROVER_EAGLE-LTSPICE_R0402
SENSOR2: BME688; ESP32_WROVER_BME680_PSON80P300X300X100-8N
SJ1: SW; SJ
TP1, TP2, TP3, TP4, TP5, TP6, TP7, TP8, TP9, TP10, TP11, TP12, TP13, TP14, TP15, TP16, TP17: TPTP20R; TP20R
U1: W25Q512JVEIQ; SON127P600X800X80-9N
U2: ESP32-C6-WROOM-1-N8; XCVR_ESP32-C6-WROOM-1-N8
U3: DS3231SN#; SOIC127P1032X265-16N
U4: MAX17048G+T10; SON50P200X200X80-9N

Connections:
3V3: C1_BAT2.1, C3.+, C9.1, D7.2 (ANODE), IC1.2 (VDD), IC4.5 (VOUT), J3.2, J4.P4 (VDD), Q2.3 (D), R1.1, R1_PINH1.2, R2-PINH1.2, R5.2, R6.2, R7.2, R8.2, R9.2, R10.2, R_BOOT.1, R_CHANGE.1, R_CL1.1, R_RESET.1, TP16.TP, U1.3 (!WP!(IO2)), U1.7 (!HOLD!/!RESET!(IO3)), U1.8 (VCC), U2.2 (3V3), U3.2 (VCC)
32KHZ: R2-PINH1.1, U2.9 (IO1), U3.1 (32KHZ)
DN: D1.4 (I/O2_2), J2.A7, J2.B7
DP: D1.6 (I/O1_2), J2.A6, J2.B6
EPD_3V3: C7.1, EPD_C5.1, J1.15, J1.16, L1.2, Q2.2 (S), TP17.TP
EPD_3V3_C: Q2.1 (G), R_CL1.2, TP13.TP, U2.18 (IO20)
EPD_BUSY: J1.9, TP9.TP, U2.26 (IO3)
EPD_CS: D6.1, J1.12, R9.1, TP10.TP, U2.11 (IO10)
EPD_DC: J1.11, R2.2, TP11.TP, U2.5 (IO5)
EPD_RST: J1.10, TP12.TP, U2.21 (IO23)
FLASH_CS: D9.1, R5.1, U1.1 (!CS), U2.12 (IO11)
GDR: J1.2, Q3.1 (G), R4.1
GND: BOOT_BUTTON.1, BOOT_BUTTON.2, C1.2, C1_BAT.2, C1_BAT1.2, C1_BAT2.2, C2.2, C2_BAT.2, C3.-, C4_USB.2, C5.2, C5_USB.2, C6.2, C7.2, C8.2, C9.2, C10.2, C10_SUPERCAP.1, CHANGE_BUTTON.1, CHANGE_BUTTON.2, C_DELAY.2, D1.2 (GND), D3.1 (K), D6.2, D8.2, D9.2, D10.2, D11.2, D12.1, EPD_C1.2, EPD_C2.2, EPD_C5.2, EPD_C6.2, EPD_C7.2, EPD_C8.2, EPD_C9.2, EPD_C10.2, EPD_C11.2, EPD_C12.2, IC1.3 (GND), IC4.2 (VSS), J1.8, J1.17, J1.MP1, J1.MP2, J2.A1, J2.A12, J2.B1, J2.B12, J2.MP1, J2.MP2, J2.MP3, J2.MP4, J3.1, J4.G1 (GND_1), J4.G2 (GND_2), J4.G3 (GND_3), J4.G4 (GND_4), MCP73831.2 (VSS), R1_PWRUSB.1, R2.1, R2-USB.2, R2-USB1.1, R2_BAT.1, R4.2, RESET_BUTTON.1, RESET_BUTTON.2, SENSOR2.1 (GND), SENSOR2.5 (SDO), SENSOR2.7 (GND), SJ1.1, TP4.TP, TP5.TP, U1.4 (GND), U1.9 (EXP), U2.1 (GND), U2.28 (GND), U2.29_1 (GND), U2.29_2 (GND), U2.29_3 (GND), U2.29_4 (GND), U2.29_5 (GND), U2.29_6 (GND), U2.29_7 (GND), U2.29_8 (GND), U2.29_9 (GND), U3.13 (GND), U4.1 (CTG), U4.4 (GND), U4.6 (QSTRT), U4.9 (EP)
GPIO8: R1.2, U2.10 (IO8)
I2C_PW: C1.1, C2.1, R1_PINH.2, R2_PINH.2, SENSOR2.2 (CSB), SENSOR2.6 (VDDIO), SENSOR2.8 (VDD), U2.17 (IO19)
INT_RTC: R1_PINH1.1, TP15.TP, U2.8 (IO0), U3.3 (SQW/!INT)
IO/BOOT: BOOT_BUTTON.3, BOOT_BUTTON.4, C6.1, R_BOOT.2, U2.15 (IO9)
IO/CHANGE: C10.1, CHANGE_BUTTON.3, CHANGE_BUTTON.4, R_CHANGE.2, U2.23 (IO15)
MISO: D12.2, J4.P7 (DAT0), R8.1, TP6.TP, U1.2 (DO(IO1)), U2.27 (IO2)
MOSI: D11.1, J1.14, J4.P3 (CMD), R7.1, TP7.TP, U1.5 (DI(IO0)), U2.7 (IO7)
unnamed: J2.B5, R2-USB.1
unnamed: J2.A5, R2-USB1.2
unnamed: C1_BAT1.1, D2.1 (CATHODE), IC4.1 (VIN), IC4.3 (CE), Q1.2 (S)
unnamed: C4.1, D3.2 (A), D4.1 (K)
unnamed: MCP73831.1 (STAT), R1_BAT.1
unnamed: CHG_LED.C, R1_BAT.2
unnamed: MCP73831.5 (PROG), R2_BAT.2
unnamed: EPD_C2.1, J1.5
unnamed: EPD_C1.1, J1.4
unnamed: EPD_C6.1, J1.18
unnamed: EPD_C7.1, J1.19
unnamed: EPD_C8.1, J1.20
unnamed: C_DELAY.1, IC1.5 (CT)
unnamed: EPD_C10.1, J1.22
unnamed: EPD_C12.1, J1.24
unnamed: D7.1 (CATHODE), R_CAPACITOR.2
PREVGH: D5.1 (K), EPD_C9.1, J1.21
PREVGL: D4.2 (A), EPD_C11.1, J1.23
RESE: J1.3, Q3.2 (S), R3.1
RESE': R3.2, SJ1.2
RESET: C5.1, IC1.1 (VOUT), RESET_BUTTON.3, RESET_BUTTON.4, R_RESET.2, U2.3 (EN)
RTC_RST: U2.16 (IO18), U3.4 (!RST)
RX: TP2.TP, U2.24 (RXD0/GPIO17)
SCK: D10.1, J1.13, J4.P5 (CLK), R6.1, TP8.TP, U1.6 (CLK), U2.6 (IO6)
SCL: J3.4, R2_PINH.1, SENSOR2.4 (SCK), U2.20 (IO22), U3.16 (SCL), U4.7 (SCL)
SDA: J3.3, R1_PINH.1, SENSOR2.3 (SDI), U2.19 (IO21), U3.15 (SDA), U4.8 (SDA)
SRC: C4.2, D5.2 (A), L1.1, Q3.3 (D)
SS_SD: D8.1, J4.P2 (CD/DAT3), R10.1, U2.4 (IO4)
TX: TP1.TP, U2.25 (TXD0/GPIO16)
USB_D+: D1.1 (I/O1_1), U2.14 (IO13)
USB_D-: D1.3 (I/O2_1), U2.13 (IO12)
VBAT: C2_BAT.1, MCP73831.3 (VBAT), Q1.3 (D), TP3.TP, U4.2 (CELL), U4.3 (VDD)
VBUS: C1_BAT.1, C4_USB.1, C5_USB.1, CHG_LED.A, D1.5 (VBUS), D2.2 (ANODE), MCP73831.4 (VIN), PFMF.050.1.2, Q1.1 (G), R1_PWRUSB.2, TP14.TP
VRTC: C8.1, C10_SUPERCAP.2, R_CAPACITOR.1, U3.14 (VBAT)
VUSB: J2.A4, J2.A9, J2.B4, J2.B9, PFMF.050.1.1

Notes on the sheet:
USB C connector & ESD protection
LDO Voltage Regulator
SD Card
Display Type Selector
E-Paper Drive Circuit
Li-Po Battery Charging Controller
ESP32 C6
E-Paper Display Header
EPD Power
Environmental Sensor BME688
Voltage Supervisor + Reset & Boot / IO Button
Battery Charge Level
RTC Module DS3231SN
Test Pads
Qwiic / Stemma QT
SPI ESD Protection Lines
External NOR Flash 64MB

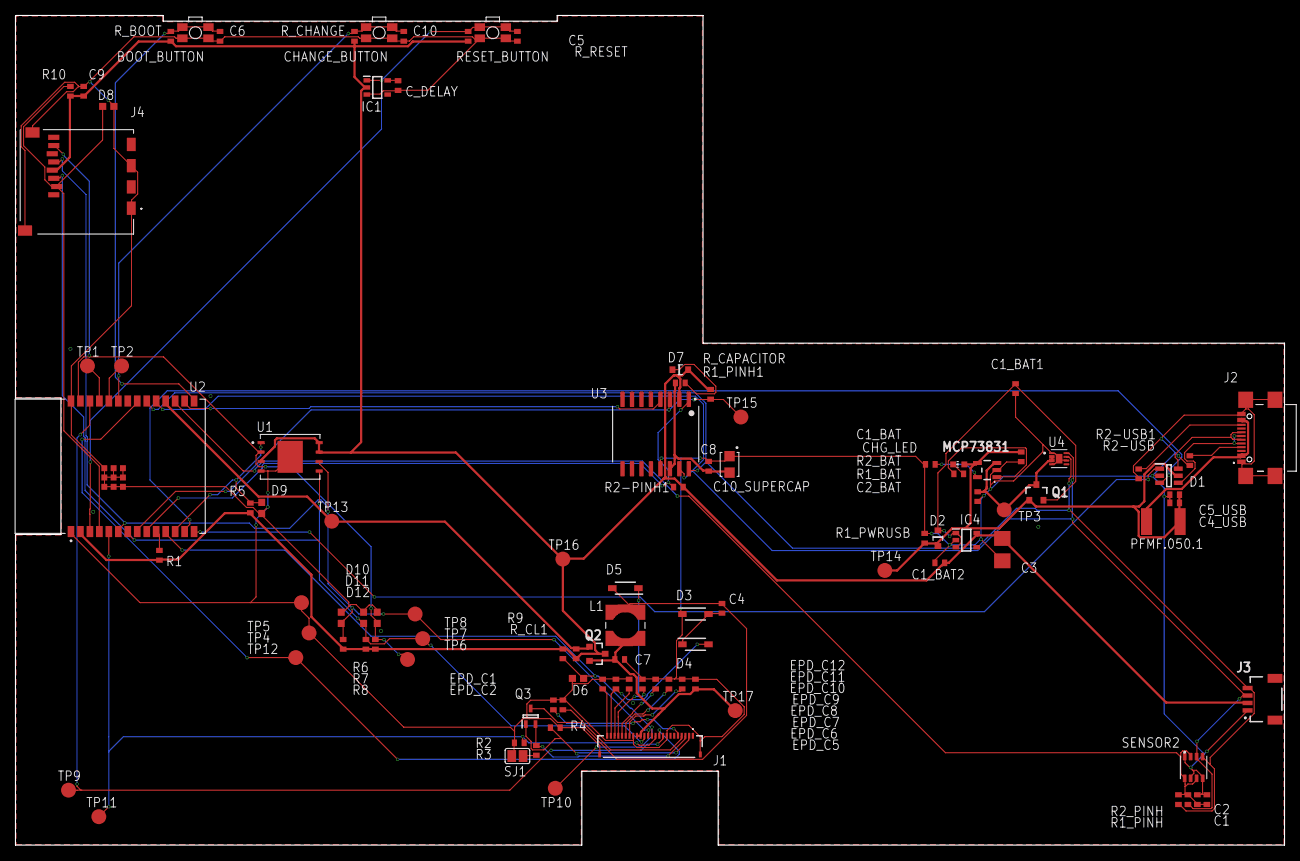
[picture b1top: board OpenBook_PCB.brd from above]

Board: 2 copper layers, 170.2 x 111.3 mm, 103 parts (0 on the bottom side), 55 nets.

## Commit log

2025-04-05 Added BOM in README.md
2025-04-05 Create LICENSE
2025-04-06 Added pin information
2025-04-06 Added files
2025-04-06 Added Block DIagram
2025-04-06 Added Hardware Description
2025-04-13 Solving the issues
2025-04-13 Solved the issues
2025-04-13 Deleted old photo

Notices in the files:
parts and their libraries:
COPYRIGHT: Copyright (C) 2024 Ultra Librarian. All rights reserved.
